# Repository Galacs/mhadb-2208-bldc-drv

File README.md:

# MHADB BLDC DRIVER

STM32F1 based 2208 size gimbal bldc foc driver controller board

## IC List

- STM32F103C8T (Main MCU)
- DRV8311 (BLDC driver)
- AS5600 (magnetic encoder)
- SN65HVD (CAN transceiver)

# Related repositories

- [Galacs/mhadb-main-board](https://github.com/Galacs/mhadb-main-board)
- [Galacs/mhadb-line-sensor](https://github.com/Galacs/mhadb-line-sensor)
- [Galacs/mhadb-firmware](https://github.com/Galacs/mhadb-firmware)

## Top preview

## Preview 3d render

## Pictures

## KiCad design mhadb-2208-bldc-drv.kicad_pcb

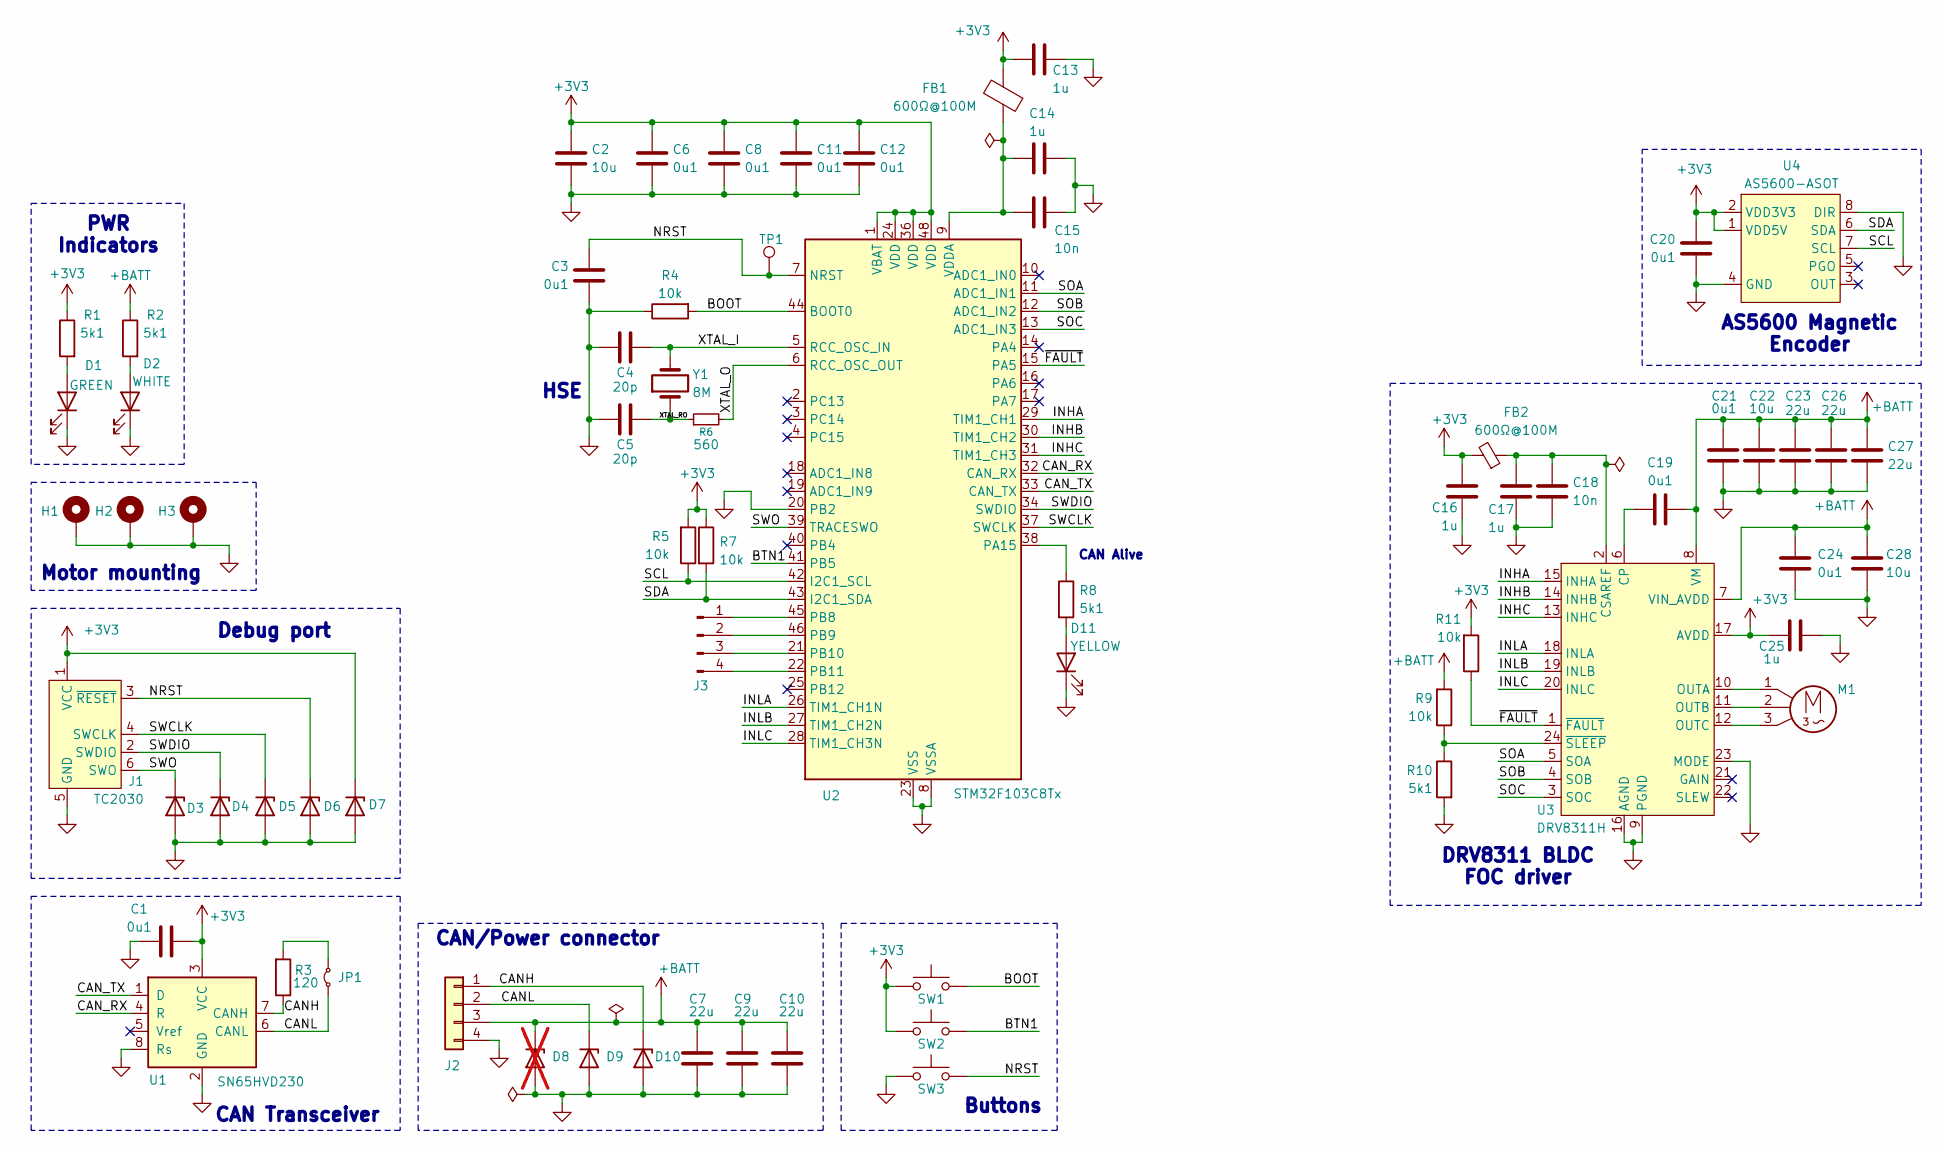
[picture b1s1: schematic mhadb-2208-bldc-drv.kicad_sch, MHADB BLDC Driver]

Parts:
C1, C3, C6, C8, C11, C12, C19, C20, C21, C24: 0u1; C_0402_1005Metric; Manufacturer Part Number CL05B104KB54PNC; JLCPCB Part # C307331
C2, C22, C28: 10u; C_0805_2012Metric; Manufacturer Part Number GRM21BR61H106KE43L; JLCPCB Part # C440198
C4, C5: 20p; C_0603_1608Metric; Manufacturer Part Number CL10C200JB8NNNC; JLCPCB Part # C1648
C7, C9, C10, C23, C26, C27: 22u; C_1206_3216Metric; Manufacturer Part Number CL31A226KAHNNNE; JLCPCB Part # C12891
C13, C14, C16, C17, C25: 1u; C_0402_1005Metric; Manufacturer Part Number CL05A105KA5NQNC; JLCPCB Part # C52923
C15, C18: 10n; C_0402_1005Metric; Manufacturer Part Number CL05B103KB5NNNC; JLCPCB Part # C15195
D1: GREEN; LED_0805_2012Metric; Manufacturer Part Number KT-0805G; JLCPCB Part # C2297
D2: WHITE; LED_0603_1608Metric; Manufacturer Part Number KT-0603W; JLCPCB Part # C2290
D3, D4, D5, D6, D7, D9, D10: H5VU10U; Diode_DFN1006; Manufacturer Part Number H5VU10U; JLCPCB Part # C22395519
D8: H5VU10U; Diode_DFN1006; Manufacturer Part Number H5VU10U; JLCPCB Part # C22395519; not fitted
D11: YELLOW; LED_0805_2012Metric; Manufacturer Part Number KT-0805Y; JLCPCB Part # C2296
FB1: 600Ω@100M; L_0805_2012Metric; Manufacturer Part Number MPZ2012S601ATD25; JLCPCB Part # C81034
FB2: 600Ω@100M; L_0805_2012Metric; Manufacturer Part Number GZ2012D101TF; JLCPCB Part # C1015
H1, H2, H3: MountingHole_Pad; MountingHole_3.2mm_M3_DIN965_Pad_Thin
J1: TC2030; Tag-Connect_TC2030-IDC-NL_2x03_P1.27mm_Vertical
J2: Conn_01x04; JST_XH_B4B-XH-A_1x04_P2.50mm_Vertical; Manufacturer Part Number B4B-XH-A(LF)(SN); JLCPCB Part # C144395
J3: Conn_01x04_Pin; PinHeader_1x04_P2.54mm_Vertical
JP1: Jumper_2_Small_Bridged; SolderJumper-2_P1.3mm_Open_RoundedPad1.0x1.5mm
M1: Motor_3_Phases; Connector_Pad_1x03
R1, R2, R8, R10: 5k1; R_0402_1005Metric; Manufacturer Part Number 0402WGF5101TCE; JLCPCB Part # C25905
R3: 120; R_1206_3216Metric; Manufacturer Part Number 1206W4F1200T5E; JLCPCB Part # C17909
R4, R5, R7, R9, R11: 10k; R_0402_1005Metric; Manufacturer Part Number 0402WGF1002TCE; JLCPCB Part # C25744
R6: 560; R_0603_1608Metric; Manufacturer Part Number 0603WAF5600T5E; JLCPCB Part # C23204
SW1, SW2, SW3: SW_Push; SW_SPST_TS-1088-xR020; Manufacturer Part Number TS-1088-AR02016; JLCPCB Part # C720477
TP1: TestPoint; TestPoint_Pad_D2.0mm
U1: SN65HVD230; SOIC-8_3.9x4.9mm_P1.27mm; Manufacturer Part Number SN65HVD230DR; JLCPCB Part # C12084
U2: STM32F103C8Tx; LQFP-48_7x7mm_P0.5mm; Manufacturer Part Number STM32F103C8T6; JLCPCB Part # C8734
U3: DRV8311H; Texas_RRW0024A_WQFN-24-1EP_2x2mm_P0.4mmThermalVias; Manufacturer Part Number DRV8311HRRWR; JLCPCB Part # C5218862
U4: AS5600-ASOT; SOIC-8_3.9x4.9mm_P1.27mm; Manufacturer Part Number AS5600-ASOT; JLCPCB Part # C499458
Y1: 8M; Crystal_SMD_5032-2Pin_5.0x3.2mm; Manufacturer Part Number X50328MSB2GI; JLCPCB Part # C115962

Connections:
+3V3: C1.1, C2.1, C6.1, C8.1, C11.1, C12.1, C13.1, C16.1, C20.1, C25.1, D7.1 (K), FB1.2, FB2.2, J1.1 (VCC), R1.1, R5.2, R7.1, R11.2, SW1.1, SW2.1, U1.3 (VCC), U2.1 (VBAT), U2.24 (VDD), U2.36 (VDD), U2.48 (VDD), U3.17 (AVDD), U4.1 (VDD5V), U4.2 (VDD3V3)
+BATT: C7.1, C9.1, C10.1, C19.2, C21.2, C22.2, C23.1, C24.2, C26.1, C27.1, C28.2, D8.1 (K), J2.3, R2.1, R9.2, U3.7 (VIN_AVDD), U3.8 (VM)
/BOOT: R4.2, SW1.2, U2.44 (BOOT0)
/BTN1: SW2.2, U2.41 (PB5)
/CANH: D10.1 (K), J2.1, R3.1, U1.7 (CANH)
/CANL: D9.1 (K), J2.2, JP1.1 (A), U1.6 (CANL)
/CAN_RX: U1.4 (R), U2.32 (CAN_RX)
/CAN_TX: U1.1 (D), U2.33 (CAN_TX)
/INHA: U2.29 (TIM1_CH1), U3.15 (INHA)
/INHB: U2.30 (TIM1_CH2), U3.14 (INHB)
/INHC: U2.31 (TIM1_CH3), U3.13 (INHC)
/INLA: U2.26 (TIM1_CH1N), U3.18 (INLA)
/INLB: U2.27 (TIM1_CH2N), U3.19 (INLB)
/INLC: U2.28 (TIM1_CH3N), U3.20 (INLC)
/NRST: C3.1, D6.1 (K), J1.3 (~RESET), SW3.2, TP1.1, U2.7 (NRST)
/SCL: R5.1, U2.42 (I2C1_SCL), U4.7 (SCL)
/SDA: R7.2, U2.43 (I2C1_SDA), U4.6 (SDA)
/SOA: U2.11 (ADC1_IN1), U3.5 (SOA)
/SOB: U2.12 (ADC1_IN2), U3.4 (SOB)
/SOC: U2.13 (ADC1_IN3), U3.3 (SOC)
/SWCLK: D5.1 (K), J1.4 (SWCLK), U2.37 (SWCLK)
/SWDIO: D4.1 (K), J1.2 (SWDIO), U2.34 (SWDIO)
/SWO: D3.1 (K), J1.6 (SWO), U2.39 (TRACESWO)
/XTAL_I: C4.1, U2.5 (RCC_OSC_IN), Y1.2
/XTAL_O: R6.2, U2.6 (RCC_OSC_OUT)
/XTAL_RO: C5.1, R6.1, Y1.1
/~FAULT: R11.1, U2.15 (PA5), U3.1 (~FAULT)
GND: C1.2, C2.2, C3.2, C4.2, C5.2, C6.2, C7.2, C8.2, C9.2, C10.2, C11.2, C12.2, C13.2, C14.2, C15.2, C16.2, C17.2, C18.2, C20.2, C21.1, C22.1, C23.2, C24.1, C25.2, C26.2, C27.2, C28.1, D1.1 (K), D2.1 (K), D3.2 (A), D4.2 (A), D5.2 (A), D6.2 (A), D7.2 (A), D8.2 (A), D9.2 (A), D10.2 (A), D11.1 (K), H1.1, H2.1, H3.1, J1.5 (GND), J2.4, R4.1, R10.2, SW3.1, U1.2 (GND), U1.8 (Rs), U2.8 (VSSA), U2.20 (PB2), U2.23 (VSS), U2.35 (VSS), U2.47 (VSS), U3.9 (PGND), U3.16 (AGND), U3.23 (MODE), U3.25 (EPAD), U4.4 (GND), U4.8 (DIR)
unnamed: D1.2 (A), R1.2
unnamed: D2.2 (A), R2.2
unnamed: D11.2 (A), R8.2
unnamed: J3.1, U2.45 (PB8)
unnamed: J3.2, U2.46 (PB9)
unnamed: J3.3, U2.21 (PB10)
unnamed: J3.4, U2.22 (PB11)
unnamed: JP1.2 (B), R3.2
unnamed: R8.1, U2.38 (PA15)
unnamed: C14.1, C15.1, FB1.1, U2.9 (VDDA)
unnamed: C19.1, U3.6 (CP)
unnamed: C17.1, C18.1, FB2.1, U3.2 (CSAREF)
unnamed: M1.1, U3.10 (OUTA)
unnamed: M1.2, U3.11 (OUTB)
unnamed: M1.3, U3.12 (OUTC)
unnamed: R9.1, R10.1, U3.24 (~SLEEP)

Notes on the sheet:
Motor mounting
PWR Indicators
Debug port
HSE
CAN/Power connector
CAN Alive
AS5600 Magnetic Encoder
DRV8311 BLDC FOC driver
CAN Transceiver
Buttons

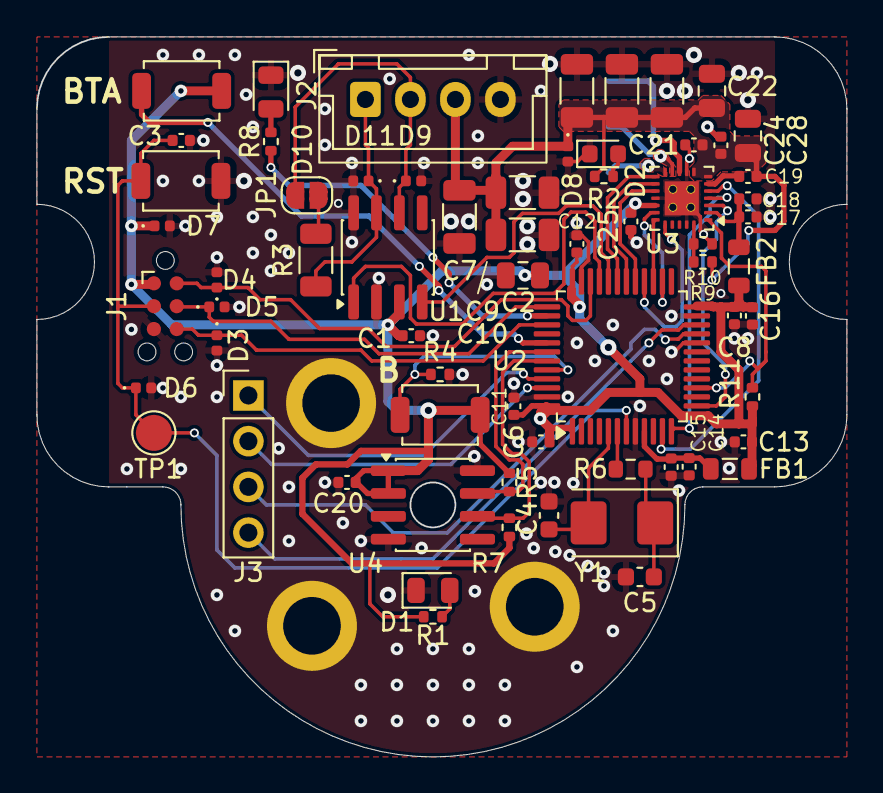
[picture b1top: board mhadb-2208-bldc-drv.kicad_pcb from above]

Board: 2 copper layers, 45.0 x 40.0 mm, 69 parts (1 on the bottom side), 44 nets.

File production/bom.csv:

Designator,Footprint,Quantity,Value,LCSC Part #
"C1, C11, C12, C19, C20, C21, C24, C3, C6, C8",0402,10,0u1,C307331
"C10, C23, C26, C27, C7, C9",1206,6,22u,C12891
"C13, C14, C16, C17, C25",0402,5,1u,C52923
"C15, C18",0402,2,10n,C15195
"C2, C22, C28",0805,3,10u,C440198
"C4, C5",0603,2,20p,C1648
D1,0805,1,GREEN,C2297
"D10, D3, D4, D5, D6, D7, D9",Diode_DFN1006,7,H5VU10U,C22395519
D11,0805,1,YELLOW,C2296
D2,0603,1,WHITE,C2290
FB1,0805,1,600Ω@100M,C81034
FB2,0805,1,600Ω@100M,C1015
"R1, R10, R2, R8",0402,4,5k1,C25905
"R11, R4, R5, R7, R9",0402,5,10k,C25744
R3,1206,1,120,C17909
R6,0603,1,560,C23204
"SW1, SW2, SW3",SW_SPST_TS-1088-xR020,3,SW_Push,C720477
U1,SOIC-8_3.9x4.9mm_P1.27mm,1,SN65HVD230,C12084
U2,LQFP-48_7x7mm_P0.5mm,1,STM32F103C8Tx,C8734
U3,Texas_RRW0024A_WQFN-24-1EP_2x2mm_P0.4mmThermalVias,1,DRV8311H,C5218862
U4,SOIC-8_3.9x4.9mm_P1.27mm,1,AS5600-ASOT,C499458
Y1,Crystal_SMD_5032-2Pin_5.0x3.2mm,1,8M,C115962

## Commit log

2026-01-08 schem: create file
2026-01-09 schem: import STM32F103C8Tx from line sensor
2026-01-09 schem: add buttons
2026-01-09 schem: add CAN/Power connector
2026-01-09 schem: add CAN transceiver
2026-01-09 schem: add SWD tag connect
2026-01-09 schem: add HT753-1 3V3 LDO
2026-01-09 schem: add DRV8311 BLDC FOC driver
2026-01-09 schem: add AS5600 magnetic encoder
2026-01-09 schem: add net classes
2026-01-09 pcb: create file and import
2026-01-09 pcb: import components from schema
2026-01-09 schem/pcb: add motor mounting holes
2026-01-09 pcb: add edge cut
2026-01-10 schem/pcb: fix DRV8311 nsleep
2026-01-10 pcb: add edge mounting keepout area
2026-01-10 pcb: initial rough placement
2026-01-10 pcb: initial components placement
2026-01-10 pcb: reduce pcb width to 45m
2026-01-10 schem: set DNP on wrongly rated tvs diode
2026-01-10 schem: add power led indicators
2026-01-10 schem: add BTN
2026-01-10 schem: add missing info to BOM
2026-01-10 schem: renumber
2026-01-10 schem: add title
2026-01-10 pcb: update from schema
2026-01-10 pcb: add gnd planes
2026-01-10 pcb: add gnd vias
2026-01-10 pcb: route crystal
2026-01-10 pcb: route SWD
2026-01-10 pcb: route CAN
2026-01-10 pcb: route DRV8311
2026-01-10 pcb: route AS5600
2026-01-10 pcb: route +BATT power
2026-01-10 pcb: route spare GPIOs
2026-01-10 pcb: route +3v3 PWR
2026-01-10 pcb: route BOOT and RST
2026-01-10 pcb: route BTN and CAN status
2026-01-10 pcb: add stitching vias
2026-01-10 pcb: run and fix DRC
2026-01-11 pcb(silkscreen): clean reference designators
2026-01-11 pcb(silkscreen): add user txt
2026-01-11 add production files
2026-01-11 pcb(silkscreen): add front buttons text
2026-01-11 pcb: add title
2026-01-11 update BOM
2026-01-11 regenerate production files
2026-01-12 pcb: update wheel 3d modell
2026-02-10 add README.md
2026-02-10 add related repo links to README.md
2026-02-10 docs: add pictures to README
